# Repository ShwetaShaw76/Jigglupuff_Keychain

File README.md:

# Jigglupuff_Keychain
Ever seen a keychain as charming that'll make you drowsy!! A jigglypuff keychain

## Schematic

## PCB

## Features
- Shape of jigglypuff can be used as a decorative item
- Circular hole at the top for attaching it to a keyring or lanyard
- LEDs attached at pupils and mouth for decoration
- Can glow at dark places using batteries

## How to build
Can be built at Kicad you just need to download the outline and image from internet.

## BOM
- 1 Battery Holder
- 3 220ohm Resistor
- 3 push button
- 3 5mm LED 
- PCB

# Slack Username

Made by `@shwetashaw006` on Slack 😁😁

Built for [Hack club solder](https://github.com/hackclub/solder)

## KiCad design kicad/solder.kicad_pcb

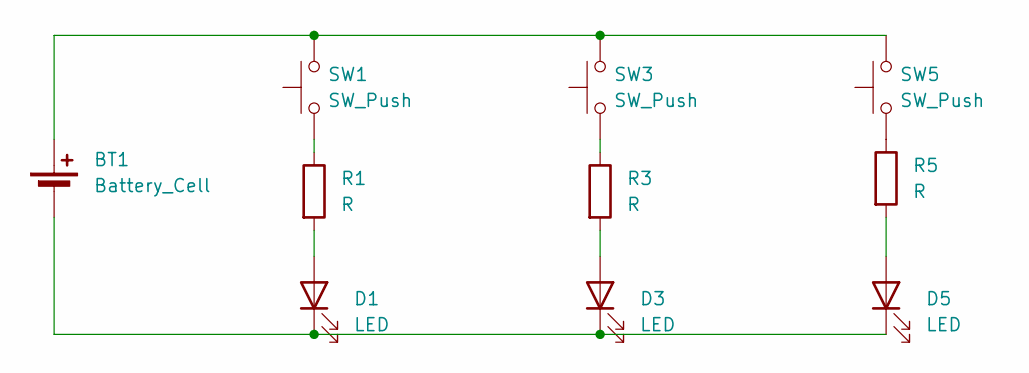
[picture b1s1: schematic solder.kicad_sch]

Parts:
BT1: Battery_Cell; BatteryHolder_Keystone_3034_1x20mm
D1, D3, D5: LED; LED_D5.0mm
R1, R3, R5: R; R_Axial_DIN0207_L6.3mm_D2.5mm_P7.62mm_Horizontal
SW1, SW3, SW5: SW_Push; SW_PUSH_6mm

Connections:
unnamed: BT1.1 (+), SW1.2, SW3.2, SW5.2
unnamed: BT1.2 (-), D1.1 (K), D3.1 (K), D5.1 (K)
unnamed: D1.2 (A), R1.2
unnamed: D3.2 (A), R3.2
unnamed: D5.2 (A), R5.2
unnamed: R1.1, SW1.1
unnamed: R3.1, SW3.1
unnamed: R5.1, SW5.1

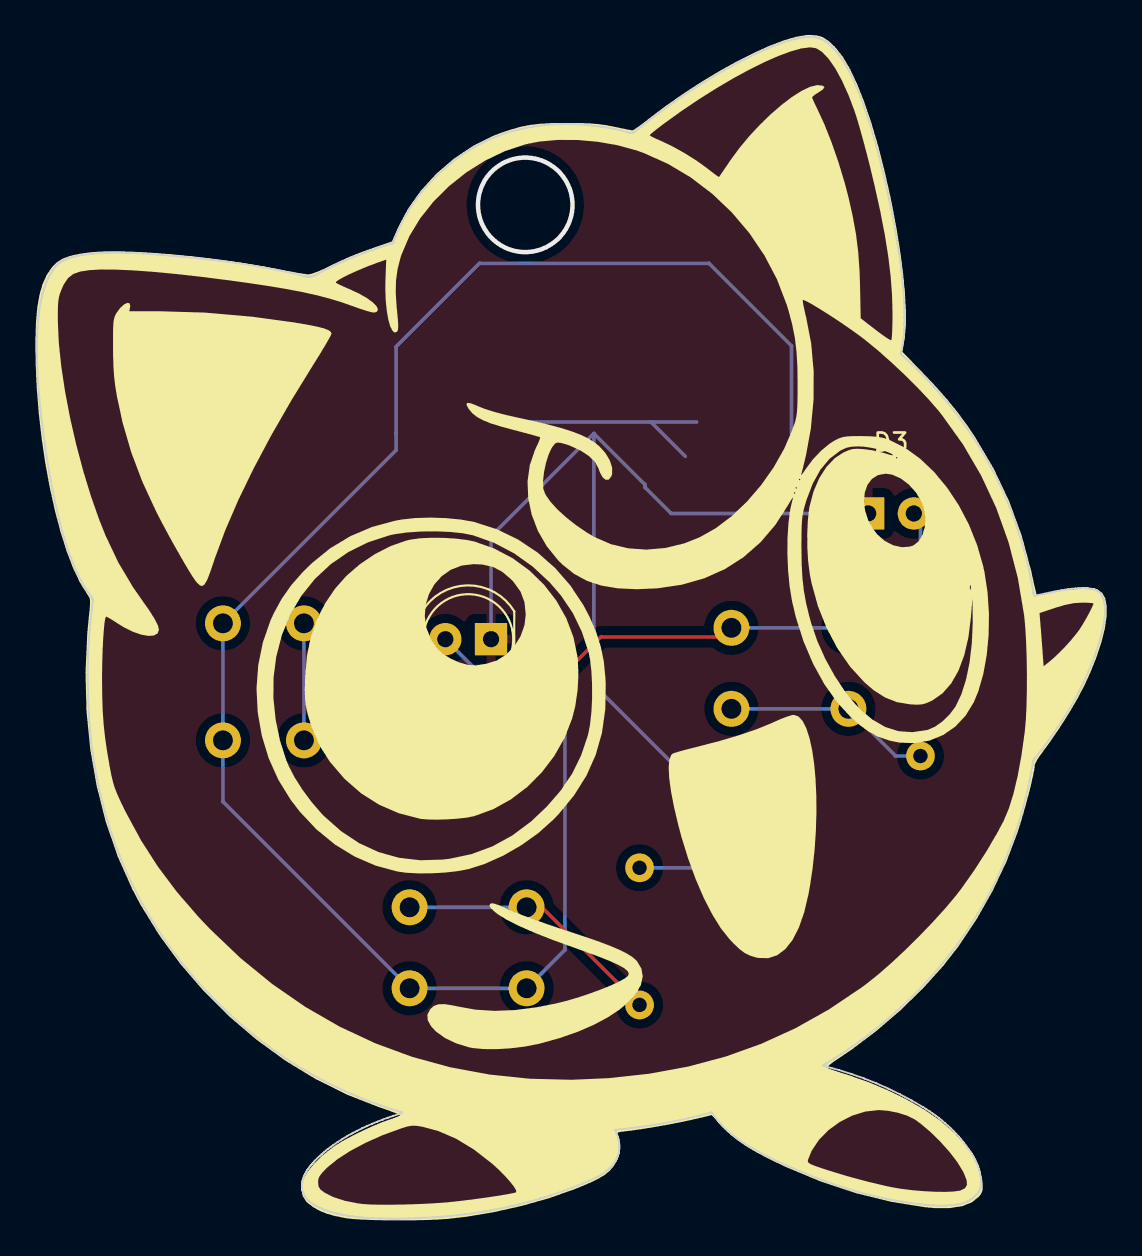
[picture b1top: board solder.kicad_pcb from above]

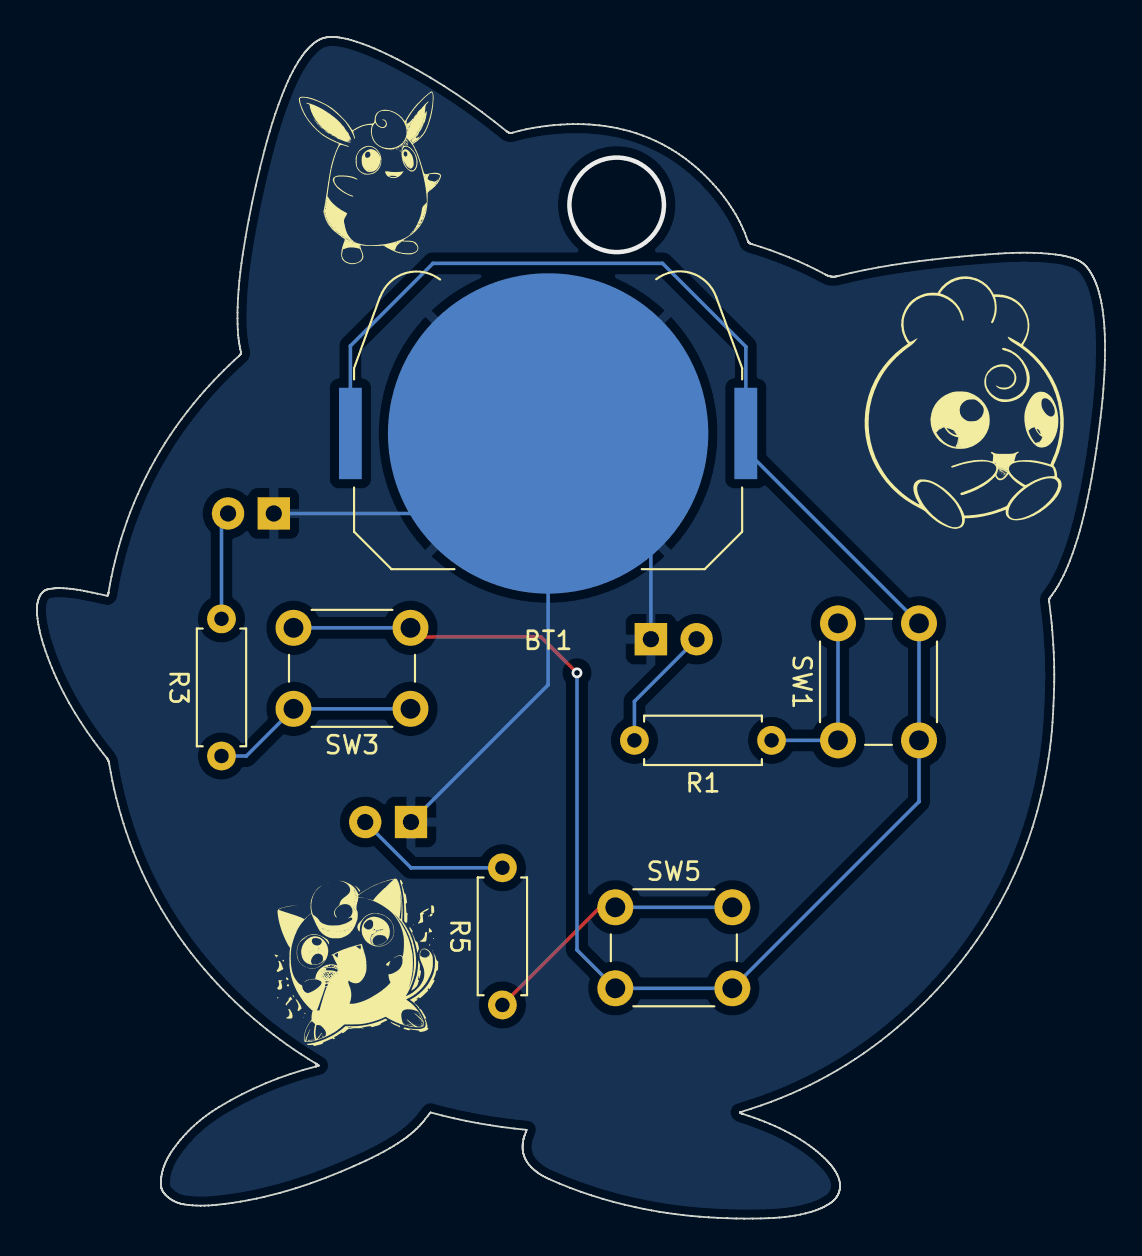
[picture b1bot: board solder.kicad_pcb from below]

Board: 2 copper layers, 59.3 x 65.7 mm, 10 parts (7 on the bottom side), 8 nets.

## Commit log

2025-06-30 made the keychain
2025-06-30 update pcb
2025-07-06 new changes
